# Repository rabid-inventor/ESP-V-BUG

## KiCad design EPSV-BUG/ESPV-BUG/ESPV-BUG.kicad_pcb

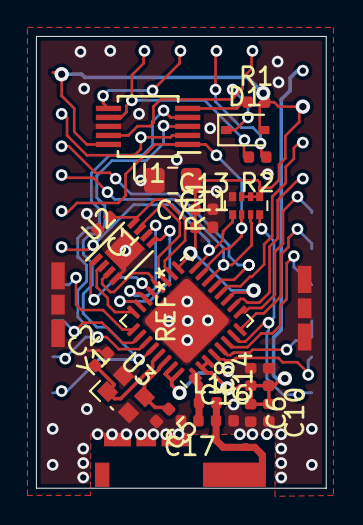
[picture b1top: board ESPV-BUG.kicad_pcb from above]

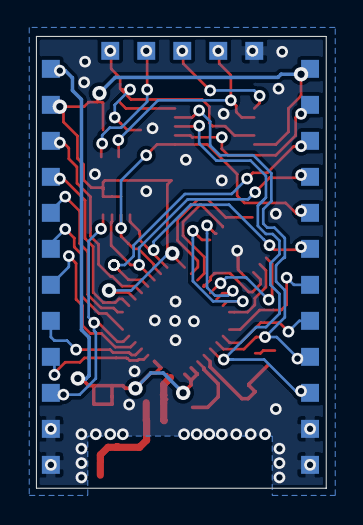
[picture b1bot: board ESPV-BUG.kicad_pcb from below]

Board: 2 copper layers, 16.1 x 25.1 mm, 25 parts (3 on the bottom side), 36 nets.

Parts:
AE1: Antenna; ACAG0801-2450Trecudedkeepout
C1, C8, C13, C14: 100nF; C_0402_1005Metric
C2, C5: 10nF; C_0402_1005Metric
C6, C11, C16, C17: 1uF; C_0402_1005Metric
C7: 10uF; C_0805_2012Metric_Pad1.15x1.40mm_HandSolder
C10: 10pF; C_0402_1005Metric
D1: D_ALT; D_SOD-323
J1, J2: Conn_01x12_Female; 01x12_pads_2mm
J3: Conn_01x05_Female; 01x5_pads_2mm
L1: L_Small; L_0402_1005Metric
R1, R2: 1k; R_0402_1005Metric
RN1: 10k 5%; R_Array_Convex_4x0402
U1: CH552E; MSOP-10_3x3mm_P0.5mm
U2: AT25xxx-MA; DFN-8-1EP_3x2mm_P0.5mm_EP1.75x1.45mm
U3: ESP32-C3; QFN-32-1EP_5x5mm_P0.5mm_EP3.45x3.45mm
Y1: 40MHz; Crystal_SMD_Abracon_ABM10-4Pin_2.5x2.0mm

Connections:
+3.3VA: C6.1, C8.1, C10.1, C14.1, J1.12, U3.2, U3.3, U3.31, U3.32
+3V3: C7.1, C11.1, C13.1, D1.2, J1.11, J2.1, R1.2, RN1.5, RN1.6, RN1.7, U1.10, U3.11, U3.17
/ANT: C17.1, L1.1, U3.1
/BLSEL: J2.5, RN1.2, U1.1, U3.15
/CHBL: J3.2, R2.1
/CHUSB+: J3.3, U1.6
/CHUSB-: J3.4, R2.2, U1.7
/CHVP: D1.1, J3.1, U1.9
/ESPUSB+: J2.8, U3.26
/ESPUSB-: J2.7, U3.25
/ESP_ENABLE: J1.3, RN1.4, U3.7
/ESP_RESET: J2.2, U1.2
/ESP_RX: J2.9, U1.4, U3.27
/ESP_TX: J2.10, U1.3, U3.28
/GP00: J1.4, U3.4
/GP01: J1.5, U3.5
/GP02: J1.6, U3.6
/GP03: J1.7, U3.8
/GP04: J1.8, U3.9
/GP05: J1.9, U3.10
/GP06: J1.10, U3.12
/GP07: J2.3, U3.13
/GP08: J2.4, RN1.3, U3.14
/GP10: J2.6, RN1.1, U3.16
/GP11: C1.1, U2.8, U3.18
/GP12: U2.7, U3.19
/GP13: U2.3, U3.20
/GP14: U2.1, U3.21
/GP15: U2.6, U3.22
/GP16: U2.5, U3.23
/GP17: U2.2, U3.24
GND: C1.2, C2.2, C5.2, C6.2, C7.2, C8.2, C10.2, C11.2, C13.2, C14.2, C16.2, C17.2, J1.1, J1.2, J2.11, J2.12, J3.5, RN1.8, U1.8, U2.4, U2.9, U3.33, Y1.2, Y1.4
unnamed: AE1.1, C16.1, L1.2
unnamed: C2.1, U3.29, Y1.1
unnamed: C5.1, U3.30, Y1.3
unnamed: R1.1, U1.5

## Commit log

2020-12-17 started
2020-12-29 general work
2021-02-12 routing finished ready for silk
